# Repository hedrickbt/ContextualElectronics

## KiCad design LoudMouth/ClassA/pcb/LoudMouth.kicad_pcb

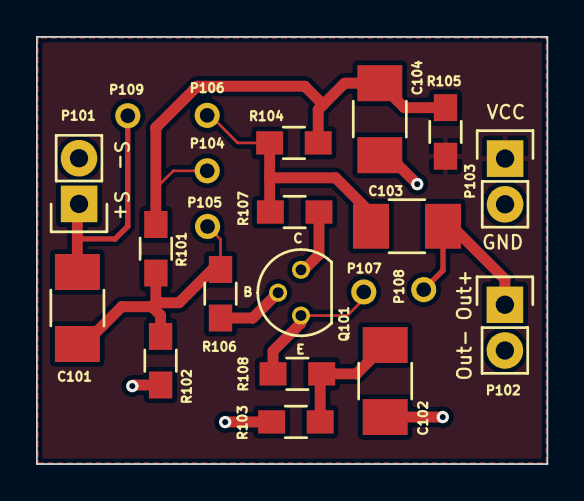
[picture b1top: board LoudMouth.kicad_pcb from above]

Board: 2 copper layers, 28.4 x 23.7 mm, 22 parts (0 on the bottom side), 11 nets.

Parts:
C101, C102, C103, C104: .82uf; C_1210_HandSoldering
P101, P102, P103: CONN_01X02; Pin_Header_Straight_1x02
P104: TP RES; TESTPOINT_1
P105: TP BAS; TESTPOINT_1
P106: TP COLL; TESTPOINT_1
P107: TP EM; TESTPOINT_1
P108: TP AMPDN; TESTPOINT_1
P109: TP INP; TESTPOINT_1
Q101: NPN; TO-92_Molded_Narrow
R101: 82k; R_0805_HandSoldering
R102: 39k; R_0805_HandSoldering
R103: 4.7k; R_0805_HandSoldering
R104: 6.8k; R_0805_HandSoldering
R105: 33; R_0805_HandSoldering
R106, R107, R108: 0; R_0805_HandSoldering

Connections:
/VCC: P103.1, R105.1
/VIN: C101.2, P101.1, P109.1
/VOUT: C103.1, P102.1, P108.1
GND: C102.1, C104.1, P101.2, P102.2, P103.2, R102.2, R103.2
unnamed: C101.1, P105.1, R101.2, R102.1, R106.2
unnamed: C102.2, R103.1, R108.2
unnamed: C103.2, P106.1, R104.2, R107.1
unnamed: C104.2, P104.1, R101.1, R104.1, R105.2
unnamed: P107.1, Q101.1, R108.1
unnamed: Q101.2, R106.1
unnamed: Q101.3, R107.2

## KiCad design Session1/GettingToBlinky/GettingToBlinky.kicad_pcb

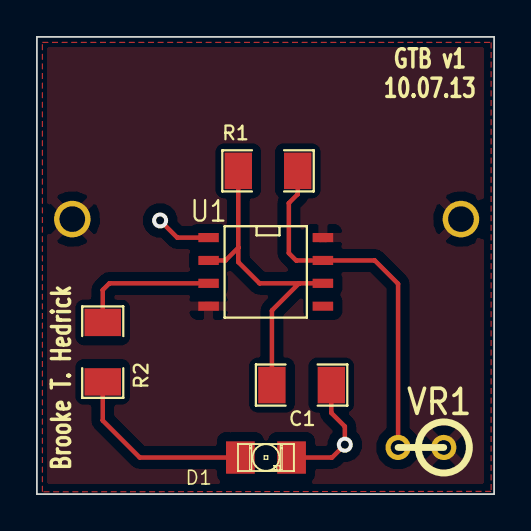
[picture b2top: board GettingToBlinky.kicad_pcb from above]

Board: 2 copper layers, 25.4 x 25.4 mm, 7 parts (1 on the bottom side), 6 nets.

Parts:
BT1: CR2032; CR2032_BK-913
C1: 1U; SM1206
D1: LED; LED-1206
R1: 470K; SM1206
R2: 1K; SM1206
U1: 7555; SO8N
VR1: LDR; R1

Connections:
GND: BT1.2, C1.2, D1.2, U1.1
unnamed: R2.1, U1.3
unnamed: D1.1, R2.2
unnamed: C1.1, R1.2, U1.2, U1.6
unnamed: R1.1, U1.7, VR1.2
VCC: BT1.1, U1.4, U1.8, VR1.1

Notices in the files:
LoudMouth/ClassA/pcb/LoudMouth.kicad_pcb:
License: CCBY
